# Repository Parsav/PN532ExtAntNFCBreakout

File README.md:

# PN532ExtAntNFCBreakout
Arduino compatible PN532 breakout board with support for external antenna. Designed with the xNT implantable chip in mind.
# Why this is here
I created this project because there was a lack of boards availiable online that featured the pn532 without having a huge internal antenna built in. These antennas aren't ideal for use with a chip such as the xNT implantable chip, becasue you can only get a read in the "sweet spots" around the corners or directly on the traces. With this board, you can connect your own external antenna via UFL connector, allowing you to connect antennas that are able to work much better with implantable chips. This board and antenna will allow you to make your xNT projects much more compact and reliable, as well as allowing you to extend the antenna away from the controller using a coax cable.

Hopefully this could transform into a board that will help people make better projects to use with their xNT much more easily.

#What it is
##The circuits
The current design is based around (and copied from) The [Keyduino](https://github.com/CITCEuraRFID/KeyDuino), which is a wonderful little board, created by people who said "Fuck NFC shields, lets just build one into an arduino!" This board has been invaluable to me in learning how to make projects using my xNT chip as well as programming it. The antenna that is built into it reads my chip pretty damn well, but its not too ideal for most projects considering you have to basically touch the controller, limiting your enclosure options. It does, however, also have a UFL conenctor on it for connecting external antennas, which is why I chose to model this design after it.

It's based around the [PN532] (https://cdn-shop.adafruit.com/datasheets/pn532ds.pdf) chip, which handles all of the NFC to serial communication, making it compatible with most development boards and DIY electronics.

##The antenna
As many people that there are with the xNT implant, there is surprisingly little documentation on using it well in DIY projects using microcontrollers. Through the [Biohack.me](http://forum.biohack.me/categories/all) forums, I was able to get in touch with user [Fred](http://forum.biohack.me/profile/15790/Fred), who recommended the [DLP-FANT](http://www.mouser.com/Search/Refine.aspx?Keyword=DLP-FANT). Fred used this antenna in his [NFC computer login](https://0xfred.wordpress.com/2015/11/26/nfc-login-2-0-finally-working/) system, where he scans his tag and has the board type in his password. He found the antenna through the work of [Mathieu Stephan](http://www.limpkin.fr/index.php?post/2014/10/07/Using-a-Standard-Coil-for-NFC-Tag-Implant-Reading), who figured out the best coil type for reading the xNT accurately through his voodoo black magic (This shit goes right over my head, so I am very grateful for his work). 

This is as far as my research has gotten me on the best way to interface with the xNT for DIY projects, and as far as I know, as far as anyone else has either. Trust me, I've looked everywhere.

# Why not make it myself?
The reason I'm putting this project on GitHub is becasue, honestly, I have no idea what I'm doing when it comes to designing a pcb. The schematic included in this repository is the first one Iv'e made, and its mostly just bits and pieces stolen from other open-source projects. I'm looking for people more skilled than I to collaborate and build upon the idea behind this board, because I think it could potentially be a very handy tool for grinders and DIYers alike.

# What you can do to help

## Proof the Schematic
Like I said, this is the first schematic I've made. and even then I barely know whats going on in it. I emailed it to the creator of the Keyduino, and thusly the original circuit itself, and he said it looked good, but the more eyes on it the better. The PN532 chip is capable of communicating via SPI, UART, and I2C, and I havent chosen which one it should use yet. If you know which one would work best, let me know.

## Layout the PCB
The reason I decided not to use the keyduino is the fact that it locks you into using an arduino Leonardo, which isnt inherently bad until you run out of memory. Any decently complicated sketch will fill that puppy up in no time. I decided to switch to the [Teensy 3.5](https://www.pjrc.com/store/teensy35.html) for its extended memory, more IO's, and built in microsd reader. My hope is to make an expansion board that could fit onto the teensy, in order to make compact, flexible, and powerful projects for my xNT transponder. 

However, dont feel like you have to do the same, if you have another layout in mind, go for it, it's all open source so do what you wish.

The board file included here has the original Keyduino circuit laid out already, but its not optimized for a standalone board, just the area it was on the leonardo. I also chopped off the internal antenna and related components, becasue we just need the connector

## Share Ideas
This has the possibility of being a very useful tool for anyone who wants to hack together stuff for their xNT, and only you guys know how to make it more useful. Contribute to its design, make it your own.

# Sidenote
this is the first public GitHub repo that I've made. If you have any pointers, shoot me a message, I'd love to hear them.

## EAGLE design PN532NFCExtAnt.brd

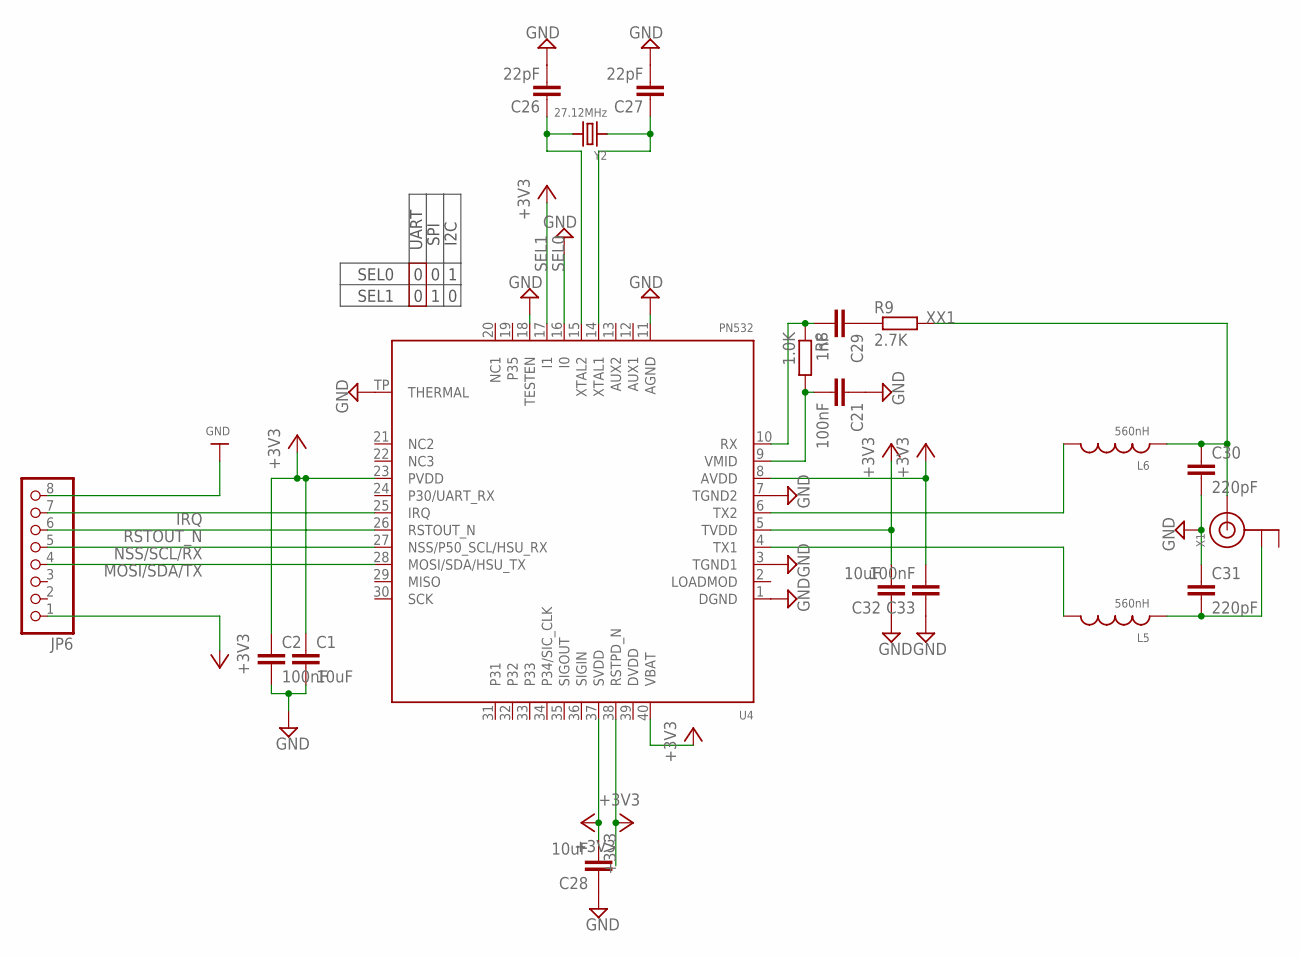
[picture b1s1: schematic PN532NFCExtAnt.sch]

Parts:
C1, C28, C32: 10uF; C0805
C2, C33: 100nF; C0805
C21: 100nF; C0603
C26, C27: 22pF; 0603-CAP
C29: 1nF; C0603
C30, C31: 220pF; C0603
JP6: HEADER-1X8ROUND; 1X08_ROUND
L5, L6: 560nH; 0805@1
R8: 1.0K; R0603
R9: 2.7K; R0603
U4: PN532; HVQFN40-6X6
X1: ANTENNA_U.FL; U.FL
Y2: 27.12MHz; CRYSTAL_3.2X2.5

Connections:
+3V3: C1.1, C2.1, C28.2, C32.2, C33.2, JP6.1, U4.5 (TVDD), U4.8 (AVDD), U4.23 (PVDD), U4.37 (SVDD), U4.38 (RSTPD_N), U4.40 (VBAT)
CON1: C31.2, L5.1, X1.1 (GND)
GND: C1.2, C2.2, C21.1, C26.1, C27.1, C28.1, C30.2, C31.1, C32.1, C33.1, JP6.8, U4.1 (DGND), U4.3 (TGND1), U4.7 (TGND2), U4.11 (AGND), U4.18 (TESTEN), U4.TP (THERMAL)
IRQ: JP6.7
MOSI/SDA/TX: JP6.4
unnamed: L5.2, U4.4 (TX1)
unnamed: L6.2, U4.6 (TX2)
unnamed: C29.1, R9.1
unnamed: C27.2, U4.14 (XTAL1), Y2.1
unnamed: C26.2, U4.15 (XTAL2), Y2.2
unnamed: C21.2, R8.2, U4.9 (VMID)
unnamed: C29.2, R8.1, U4.10 (RX)
NSS/SCL/RX: JP6.5
RSTOUT_N: JP6.6
SEL0: U4.16 (I0)
SEL1: U4.17 (I1)
XX1: C30.1, L6.1, R9.2, X1.3 (SIGNAL)

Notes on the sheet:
SEL0
SEL1
UART
SPI
I2C

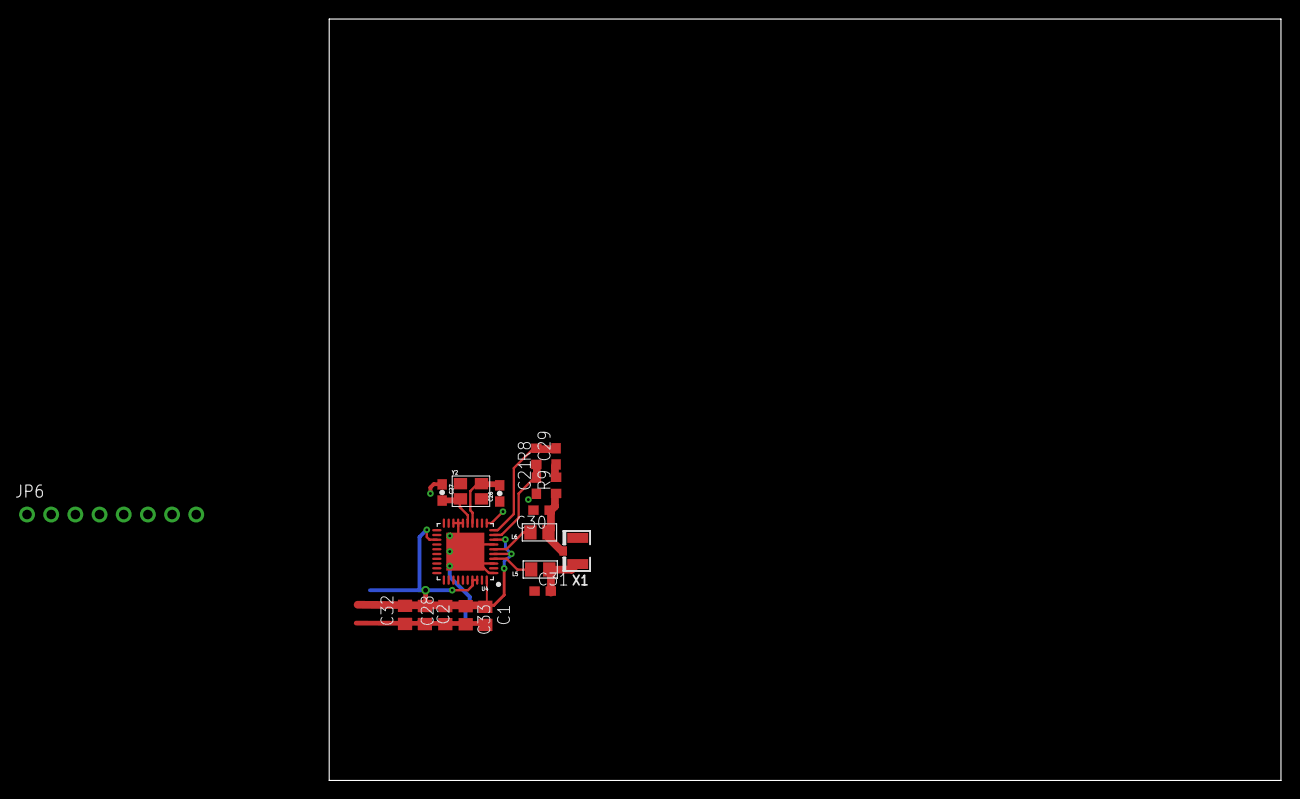
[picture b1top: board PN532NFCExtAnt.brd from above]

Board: 2 copper layers, 100.0 x 80.0 mm, 19 parts (0 on the bottom side), 11 nets.

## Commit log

2016-12-07 Update README.md
    Initial commit
